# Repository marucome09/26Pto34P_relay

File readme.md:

# 26Pto34P_relay

This is 26P FDD I/F(Mitsumi/Newtronics D357B) convert to FDD for PC(or a gotek with FlashFloppy)compatible.

(26P I/F used to Yamaha SY77/SY99/V50)

ミツミ D357B FDDの26Pinの信号線を、PC用34Pに変換するボードです。

(Yamaha SY77/SY99/V50に使用されています)

注意：この機器の取り付けによって起きたいかなるトラブルに対しても、当方は（スイッチサイエンス様で販売いただいている製品版についての製品不良時の製品交換以外）一切の責任を負いかねます。取り付けに際しては細心の注意を払い、慎重に取り付けてください。

※なお、写真は試作品です。製品版と多少異なる場合があります。

FDDに直接取り付けるアダプタータイプ26Pto34P_convもあります。

# Features　おすすめポイント

- Designed to be attached directly to FDD(or emulator).

- FDDの後方にマージンがない場合や、FDD直接接続アダプタータイプでは取り付けられないインターフェース直上に電源コネクタがあるタイプ（ミツミD353M3Dなど）でも、比較的対応しやすいアダプタータイプです。

- 純正に比べて小型なので、貼り付ける場所の自由度が非常に高いです。

- 純正の回路(XS051)と互換性があります。通常のPC用2モードFDDのほか、HxC fot Gotek、 FlashFloppy（Gotekエミュレーターのファームウェア書き換え版）にも対応します。

注意2：Usageでも説明していますが、必ず取り付け面の絶縁処理を行って取り付けてください。　

スイッチサイエンス様より発売される製品版は、絶縁処理を行っておりませんので、両面テープや絶縁テープなどでしっかり絶縁を行ったうえで、脱落しないようしっかり取り付けてください。

写真にあります電源部のコネクタは製品版ではオミットされておりますのでご了承ください。

同様に機器＝変換ボード、変換ボード＝FDD(FDDエミュレーター）間のケーブル（26ピンフラットケーブル、34ピンフラットケーブル）もお客様でご用意ください。製品版にはついておりません。

参考程度に必要なケーブルの長さ（多少冗長分も含まれますが、最終的な長さはお客様で実際に御確認ください）は、Usageに書きました。

# Requirement 制作に必要な部品

34P(17x2) pin-header or box-header  / 34ピン　ピンヘッダもしくはボックスヘッダ（FDD側 I/Fケーブル用）

26P(13x2) box-header /　26ピン ボックスヘッダ（26P I/Fケーブル用）

26Pin Flat-Cable with connectors / 26ピンフラットケーブル（両端にコネクタのついているもの）

34Pin Flat-Cable with connectors / 34ピンフラットケーブル（両端にコネクタのついているもの）

（必要な長さは機種によって違うためそれぞれの機種で確認のこと）

2P EI pin-header / 2P EI ピンヘッダ（ボードからの電源取り出し用）※

2P EI connector housing & contact / 2P EIコネクタハウジング＆コンタクト（ボードからの電源取り出し用）※

4P EI connector housing & contact / 4P EIコネクタハウジング＆コンタクト（FDD電源用）

Power Cable(必要な長さは機種によって違うためそれぞれの機種で確認のこと)

※他のコネクタでも代用可能、また基板直付けでもOK

# Making

コネクタ類を写真のようにはんだ付けします。

ボックスヘッダの取り付けは、26Pも、34Pも、切り欠きが下側（奇数ピン側）になるようにしてください。

電源の２Pコネクタは、上側が＋極になっています。それに合わせてケーブルを付けます。（２Pのコネクタヘッダをつけてもいいと思います、スイッチサイエンス様で販売の製品版はケーブル直付になります）

写真はテスト品なのでホットボンドがついていて見にくいですが、基板左（上）側が+、34Pコネクタ側が-になっています。

上に合わせてケーブルを作成し取り付けて完成です。

なお、FDD(もしくはエミュレーター）側の電源コネクタはこのように制作します。

小型なので、完成するとほぼケーブルでみえなくなります。（写真は試作品ですので電源コネクタ、およびコネクタのハンダ穴の位置が少し違います）

# Usage

使い方はXS051と同様、本体内のどこかに両面テープで、金属部分が直接接触しないように、強力両面テープや、絶縁テープなどで絶縁処理を行い、脱落しないよう強力両面テープなどで機体内に貼り付けて使用します。

26ピンフラットケーブルの必要な長さは、V50で約20~25cm程度、SY77で15cmから20cm程度、34ピンフラットケーブルのほうは、全機種だいたい20cm程度です。あくまで参考ですのでお客様で実際に確認して取り付けてください。

# Note

・信号線はDS1固定のため、DS0で動作するFDDの場合はDS1に設定を変更する必要があります。

・絶縁処理はされていませんので（Making参照のこと）、必ず基板裏面ははんだ付けのあとはショート防止もかねて、できうる限り強力タイプの、厚手の両面テープを使用いただくことを推奨します。他の電気箇所、金属部分への接触をしないようにとりつけてください。

・このFDDは通常のタイプ（デスクトップ用）のFDD（PC互換機用34Pピンヘッダタイプ）を想定して制作してあります。

・一部FDDで動作しない可能性があります。

・FDDはPC用ですので、2HDには対応していますが、本体が対応していないため2DD専用として動作します。
そのため、２HDディスクは使用しないでください。

☆なお、下記のFDDでチェックはパスしています（これ以外のFDDでも現物ご送付いただければ確認します、一度ご連絡ください）

Y-E DATA YD-702D

Sumsung SFD-321B

Mitsumi D353M3D

# License

This Product is CC BY-NC-SA 4.0

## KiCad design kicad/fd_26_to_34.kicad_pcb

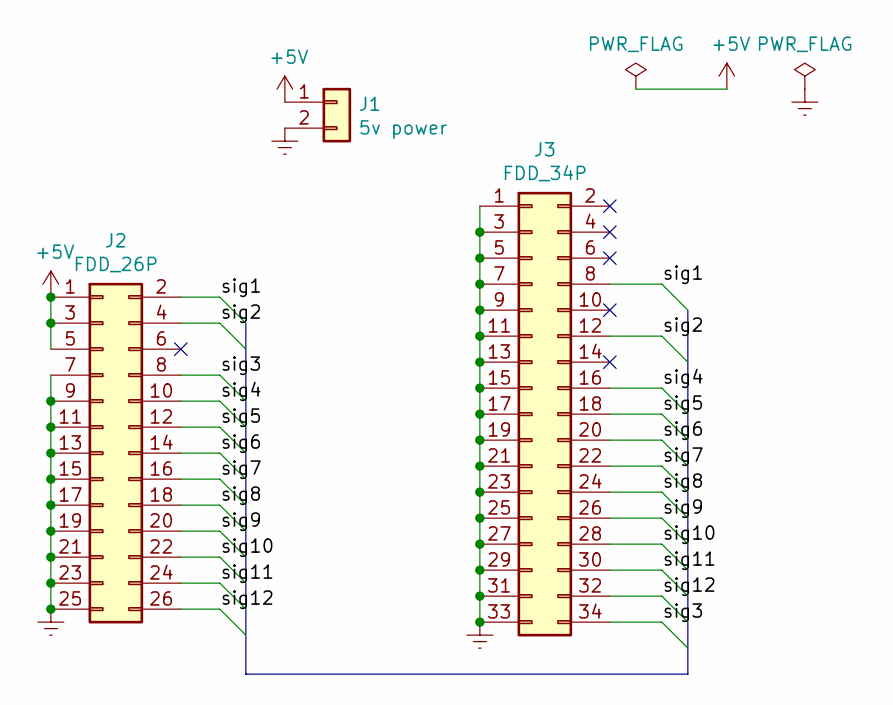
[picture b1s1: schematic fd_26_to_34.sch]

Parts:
J1: 5v power; PinHeader_1x02_P2.54mm_Vertical
J2: FDD_26P; PinHeader_2x13_P2.54mm_Vertical
J3: FDD_34P; PinHeader_2x17_P2.54mm_Vertical

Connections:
+5V: J1.1, J2.1, J2.3, J2.5
/sig1: J2.2, J3.8
/sig2: J2.4, J3.12
/sig3: J2.8, J3.34
/sig4: J2.10, J3.16
/sig5: J2.12, J3.18
/sig6: J2.14, J3.20
/sig7: J2.16, J3.22
/sig8: J2.18, J3.24
/sig9: J2.20, J3.26
/sig10: J2.22, J3.28
/sig11: J2.24, J3.30
/sig12: J2.26, J3.32
Earth: J1.2, J2.7, J2.9, J2.11, J2.13, J2.15, J2.17, J2.19, J2.21, J2.23, J2.25, J3.1, J3.3, J3.5, J3.7, J3.9, J3.11, J3.13, J3.15, J3.17, J3.19, J3.21, J3.23, J3.25, J3.27, J3.29, J3.31, J3.33

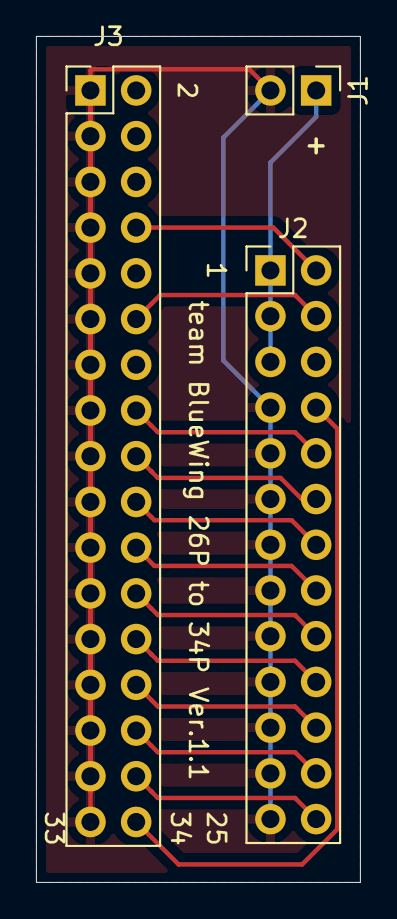
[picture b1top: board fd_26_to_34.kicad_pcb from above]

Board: 2 copper layers, 18.0 x 47.0 mm, 3 parts (0 on the bottom side), 14 nets.

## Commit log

2020-07-27 product
2025-06-06 Delete kicad/fd_26_to_34.kicad_pcb
    protect
